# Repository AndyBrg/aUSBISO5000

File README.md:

# aUSBISO5000
5kV USB2.0 Isolator with 200mA supply and speed 12Mbit/s

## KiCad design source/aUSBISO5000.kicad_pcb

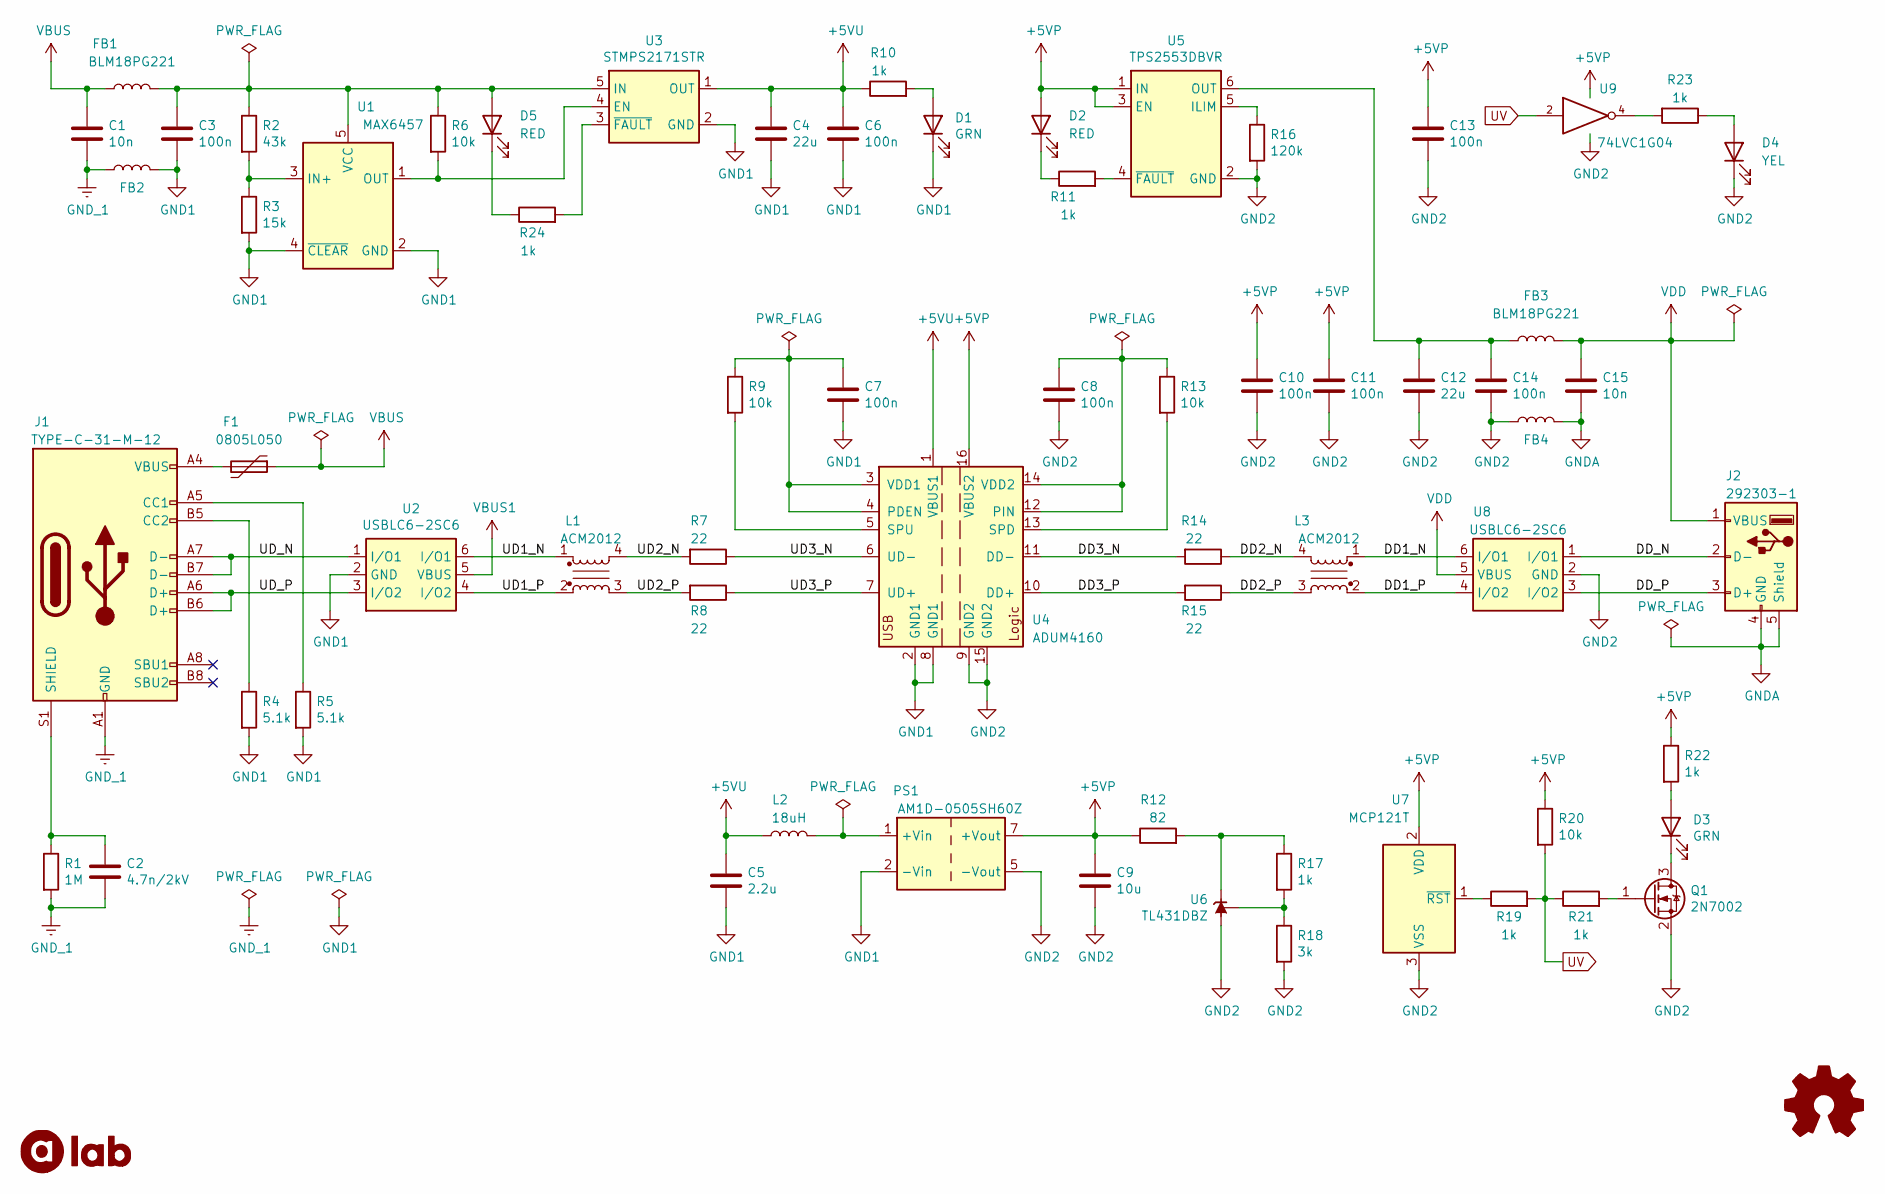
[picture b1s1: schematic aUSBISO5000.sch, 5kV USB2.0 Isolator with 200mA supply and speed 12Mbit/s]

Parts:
C1, C15: 10n; C_0603_1608Metric_Pad1.08x0.95mm_HandSolder; Part Number CC0603JRX7R9BB103
C2: 4.7n/2kV; C_1812_4532Metric_Pad1.57x3.40mm_HandSolder; Part Number CC1812KKX7RDBB472
C3, C6, C7, C8, C10, C11, C13, C14: 100n; C_0603_1608Metric_Pad1.08x0.95mm_HandSolder; Part Number CC0603JRX7R9BB104
C4, C12: 22u; C_1206_3216Metric_Pad1.33x1.80mm_HandSolder; Part Number CL31A226KAHNNNE
C5: 2.2u; C_1206_3216Metric_Pad1.33x1.80mm_HandSolder; Part Number CL31B225KCHSNNE
C9: 10u; C_1206_3216Metric_Pad1.33x1.80mm_HandSolder; Part Number CC1206KKX7R7BB106
D1, D3: GRN; LED_0603_1608Metric_Pad1.05x0.95mm_HandSolder; Part Number KP-1608CGCK
D2, D5: RED; LED_0603_1608Metric_Pad1.05x0.95mm_HandSolder; Part Number KP-1608SURCK
D4: YEL; LED_0603_1608Metric_Pad1.05x0.95mm_HandSolder; Part Number KP-1608SYC
F1: 0805L050; Fuse_0805_2012Metric_Pad1.15x1.40mm_HandSolder; Part Number 0805L050WR
FB1, FB2, FB3, FB4: BLM18PG221; L_0603_1608Metric_Pad1.05x0.95mm_HandSolder; Part Number BLM18PG221SN1D
J1: TYPE-C-31-M-12; USB_C_Receptacle_HRO_TYPE-C-31-M-12; Part Number TYPE-C-31-M-12
J2: 292303-1; USB_A_TE_292303-1; Part Number 292303-1
L1, L3: ACM2012; Part Number ACM2012-900-2P-T002
L2: 18uH; INDP5858X480N; Part Number SDR0604-180YL
PS1: AM1D-0505SH60Z; Converter_DCDC_AIMTEC_AM1D-xxxxxxxxZ3000-6200; Part Number AM1D-0505SH60Z
Q1: 2N7002; SOT-23; Part Number 2N7002
R1: 1M; R_1206_3216Metric_Pad1.30x1.75mm_HandSolder; Part Number RC1206FR-071ML
R2: 43k; R_0603_1608Metric_Pad0.98x0.95mm_HandSolder; Part Number RC0603FR-0743KL
R3: 15k; R_0603_1608Metric_Pad0.98x0.95mm_HandSolder; Part Number RC0603FR-0715KL
R4, R5: 5.1k; R_0603_1608Metric_Pad0.98x0.95mm_HandSolder; Part Number RC0603FR-075K1L
R6, R9, R13, R20: 10k; R_0603_1608Metric_Pad0.98x0.95mm_HandSolder; Part Number RC0603FR-0710KL
R7, R8, R14, R15: 22; R_0603_1608Metric_Pad0.98x0.95mm_HandSolder; Part Number RC0603FR-0722RL
R10, R11, R17, R19, R21, R22, R23, R24: 1k; R_0603_1608Metric_Pad0.98x0.95mm_HandSolder; Part Number RC0603FR-071KL
R12: 82; R_0805_2012Metric_Pad1.20x1.40mm_HandSolder; Part Number RC0805FR-0782RL
R16: 120k; R_0603_1608Metric_Pad0.98x0.95mm_HandSolder; Part Number RC0603FR-07120KL
R18: 3k; R_0603_1608Metric_Pad0.98x0.95mm_HandSolder; Part Number RC0603FR-073KL
U1: MAX6457; SOT-23-5; Part Number MAX6457UKD3C+T
U2, U8: USBLC6-2SC6; SOT-23-6; Part Number USBLC6-2SC6
U3: STMPS2171STR; SOT-23-5_HandSoldering; Part Number STMPS2171STR
U4: ADUM4160; SOIC-16W_7.5x10.3mm_P1.27mm; Part Number ADUM4160BRIZ
U5: TPS2553DBVR; SOT-23-6_Handsoldering; Part Number TPS2553DBVR
U6: TL431DBZ; SOT-23; Part Number TL431BIDBZR
U7: MCP121T; SOT-23; Part Number MCP121T-475E/TT
U9: 74LVC1G04; SOT-23-5_HandSoldering; Part Number SN74LVC1G04DBVR

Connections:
+5V: C4.1, C5.1, C6.1, L2.1, R10.1, U3.1 (OUT), U4.1 (VBUS1)
+5VP: C9.1, C10.1, C11.1, C13.1, D2.2 (A), PS1.7 (+Vout), R12.1, R20.1, R22.1, U4.16 (VBUS2), U5.1 (IN), U5.3 (EN), U7.2 (VDD), U9.5 (VCC)
/DD1_N: L3.1, U8.6 (I/O1)
/DD1_P: L3.2, U8.4 (I/O2)
/DD2_N: L3.4, R14.1
/DD2_P: L3.3, R15.1
/DD3_N: R14.2, U4.11 (DD-)
/DD3_P: R15.2, U4.10 (DD+)
/DD_N: J2.2 (D-), U8.1 (I/O1)
/DD_P: J2.3 (D+), U8.3 (I/O2)
/UD1_N: L1.1, U2.6 (I/O1)
/UD1_P: L1.2, U2.4 (I/O2)
/UD2_N: L1.4, R7.2
/UD2_P: L1.3, R8.2
/UD3_N: R7.1, U4.6 (UD-)
/UD3_P: R8.1, U4.7 (UD+)
/UD_N: J1.A7 (D-), J1.B7 (D-), U2.1 (I/O1)
/UD_P: J1.A6 (D+), J1.B6 (D+), U2.3 (I/O2)
Earth: C1.2, C2.2, FB2.1, J1.A1 (GND), J1.A12 (GND), J1.B1 (GND), J1.B12 (GND), R1.2
GND: C8.2, C9.2, C10.2, C11.2, C12.2, C13.2, C14.2, D4.1 (K), FB4.1, PS1.5 (-Vout), Q1.2 (S), R16.2, R18.2, U4.9 (GND2), U4.15 (GND2), U5.2 (GND), U6.3 (A), U7.3 (VSS), U8.2 (GND), U9.3 (GND)
GND1: C3.2, C4.2, C5.2, C6.2, C7.2, D1.1 (K), FB2.2, PS1.2 (-Vin), R3.2, R4.2, R5.2, U1.2 (GND), U1.4 (~CLEAR), U2.2 (GND), U3.2 (GND), U4.2 (GND1), U4.8 (GND1)
GNDA: C15.2, FB4.2, J2.4 (GND), J2.5 (Shield)
unnamed: C2.1, J1.S1 (SHIELD), R1.1
unnamed: C3.1, D5.2 (A), FB1.2, R2.1, R6.1, U1.5 (VCC), U3.5 (IN)
unnamed: C7.1, R9.1, U4.3 (VDD1), U4.4 (PDEN)
unnamed: C8.1, R13.1, U4.12 (PIN), U4.14 (VDD2)
unnamed: C12.1, C14.1, FB3.2, U5.6 (OUT)
unnamed: D1.2 (A), R10.2
unnamed: D2.1 (K), R11.1
unnamed: D3.1 (K), Q1.3 (D)
unnamed: D3.2 (A), R22.2
unnamed: D4.2 (A), R23.1
unnamed: D5.1 (K), R24.1
unnamed: F1.2, J1.A4 (VBUS), J1.A9 (VBUS), J1.B4 (VBUS), J1.B9 (VBUS)
unnamed: J1.A5 (CC1), R5.1
unnamed: J1.B5 (CC2), R4.1
unnamed: L2.2, PS1.1 (+Vin)
unnamed: Q1.1 (G), R21.2
unnamed: R2.2, R3.1, U1.3 (IN+)
unnamed: R6.2, U1.1 (OUT), U3.4 (EN)
unnamed: R9.2, U4.5 (SPU)
unnamed: R11.2, U5.4 (~FAULT)
unnamed: R12.2, R17.1, U6.1 (K)
unnamed: R13.2, U4.13 (SPD)
unnamed: R16.1, U5.5 (ILIM)
unnamed: R17.2, R18.1, U6.2 (REF)
unnamed: R19.1, U7.1 (~RST)
unnamed: R23.2, U9.4
unnamed: R24.2, U3.3 (~FAULT)
UV: R19.2, R20.2, R21.1, U9.2
VDD: C15.1, FB3.1, J2.1 (VBUS), U8.5 (VBUS)

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
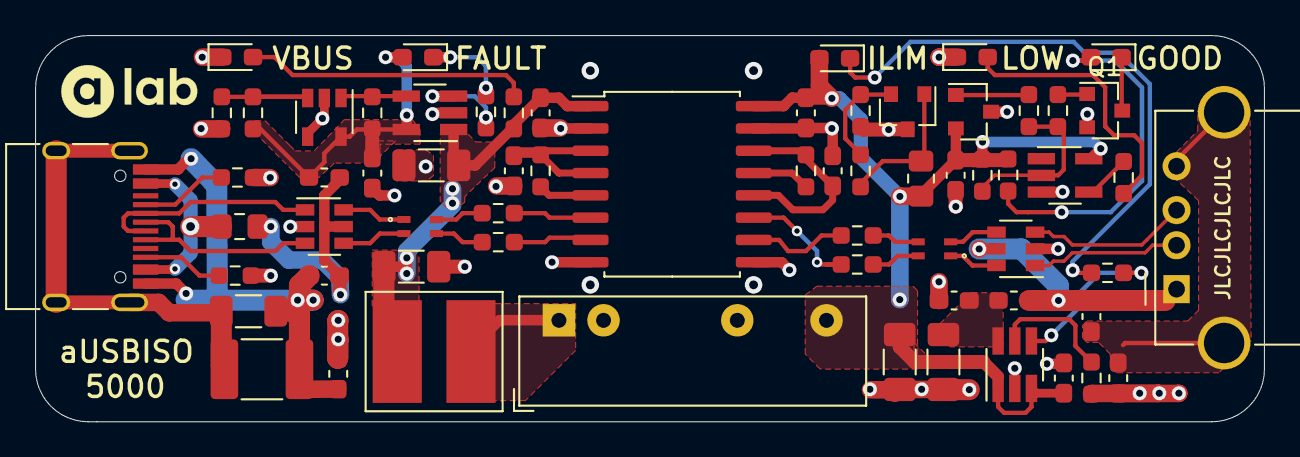
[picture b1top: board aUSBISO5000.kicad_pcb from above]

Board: 2 copper layers, 70.0 x 22.0 mm, 65 parts (0 on the bottom side), 52 nets.

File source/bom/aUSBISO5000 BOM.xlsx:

| BOM | aUSBISO5000 | v1.0
 | References | Part Number | Value | Footprint | Quantity
1 | C1, C15 | CC0603JRX7R9BB103 | 10n | C_0603_1608Metric_Pad1.08x0.95mm_HandSolder | 2
2 | C3, C6, C7, C8, C10, C11, C13, C14 | CC0603JRX7R9BB104 | 100n | C_0603_1608Metric_Pad1.08x0.95mm_HandSolder | 8
3 | C9 | CC1206KKX7R7BB106 | 10u | C_1206_3216Metric_Pad1.33x1.80mm_HandSolder | 1
4 | C2 | CC1812KKX7RDBB472 | 4.7n/2kV | C_1812_4532Metric_Pad1.57x3.40mm_HandSolder | 1
5 | C4, C12 | CL31A226KAHNNNE | 22u | C_1206_3216Metric_Pad1.33x1.80mm_HandSolder | 2
6 | C5 | CL31B225KCHSNNE | 2.2u | C_1206_3216Metric_Pad1.33x1.80mm_HandSolder | 1
7 | R6, R9, R13, R20 | RC0603FR-0710KL | 10k | R_0603_1608Metric_Pad0.98x0.95mm_HandSolder | 4
8 | R16 | RC0603FR-07120KL | 120k | R_0603_1608Metric_Pad0.98x0.95mm_HandSolder | 1
9 | R3 | RC0603FR-0715KL | 15k | R_0603_1608Metric_Pad0.98x0.95mm_HandSolder | 1
10 | R10, R11, R17, R19, R21, R22, R23, R24 | RC0603FR-071KL | 1k | R_0603_1608Metric_Pad0.98x0.95mm_HandSolder | 8
11 | R7, R8, R14, R15 | RC0603FR-0722RL | 22 | R_0603_1608Metric_Pad0.98x0.95mm_HandSolder | 4
12 | R2 | RC0603FR-0743KL | 43k | R_0603_1608Metric_Pad0.98x0.95mm_HandSolder | 1
13 | R18 | RC0603FR-073KL | 3k | R_0603_1608Metric_Pad0.98x0.95mm_HandSolder | 1
14 | R4, R5 | RC0603FR-075K1L | 5.1k | R_0603_1608Metric_Pad0.98x0.95mm_HandSolder | 2
15 | R12 | RC0805FR-0782RL | 82 | R_0805_2012Metric_Pad1.20x1.40mm_HandSolder | 1
16 | R1 | RC1206FR-071ML | 1M | R_1206_3216Metric_Pad1.30x1.75mm_HandSolder | 1
17 | L1, L3 | ACM2012-900-2P-T002 | ACM2012 | ACM2012 | 2
18 | L2 | SDR0604-180YL | 18uH | INDP5858X480N | 1
19 | D1, D3 | KP-1608CGCK | GRN | LED_0603_1608Metric_Pad1.05x0.95mm_HandSolder | 2
20 | D2, D5 | KP-1608SURCK | RED | LED_0603_1608Metric_Pad1.05x0.95mm_HandSolder | 2
21 | D4 | KP-1608SYC | YEL | LED_0603_1608Metric_Pad1.05x0.95mm_HandSolder | 1
22 | U4 | ADUM4160BRIZ | ADUM4160 | SOIC-16W_7.5x10.3mm_P1.27mm | 1
23 | U1 | MAX6457UKD3C+T | MAX6457 | SOT-23-5 | 1
24 | U7 | MCP121T-475E/TT | MCP121T | SOT-23 | 1
25 | U9 | SN74LVC1G04DBVR | 74LVC1G04 | SOT-23-5_HandSoldering | 1
26 | U3 | STMPS2171STR | STMPS2171STR | SOT-23-5_HandSoldering | 1
27 | U6 | TL431BIDBZR | TL431DBZ | SOT-23 | 1
28 | U5 | TPS2553DBVR | TPS2553DBVR | SOT-23-6_Handsoldering | 1
29 | U2, U8 | USBLC6-2SC6 | USBLC6-2SC6 | SOT-23-6 | 2
30 | F1 | 0805L050WR | 0805L050 | Fuse_0805_2012Metric_Pad1.15x1.40mm_HandSolder | 1
31 | PS1 | AM1D-0505SH60Z | AM1D-0505SH60Z | Converter_DCDC_AIMTEC_AM1D-xxxxxxxxZ3000-6200 | 1
32 | Q1 | 2N7002 | 2N7002 | SOT-23 | 1
33 | FB1, FB2, FB3, FB4 | BLM18PG221SN1D | BLM18PG221 | L_0603_1608Metric_Pad1.05x0.95mm_HandSolder | 4
34 | J2 | 292303-1 | 292303-1 | USB_A_TE_292303-1 | 1
35 | J1 | TYPE-C-31-M-12 | TYPE-C-31-M-12 | USB_C_Receptacle_HRO_TYPE-C-31-M-12 | 1

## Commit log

2021-10-06 Init commit
